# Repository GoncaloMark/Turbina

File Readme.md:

# Turbina '23

Componente Hardware e Software para Turbinas Tesup carregarem baterias de 12V.

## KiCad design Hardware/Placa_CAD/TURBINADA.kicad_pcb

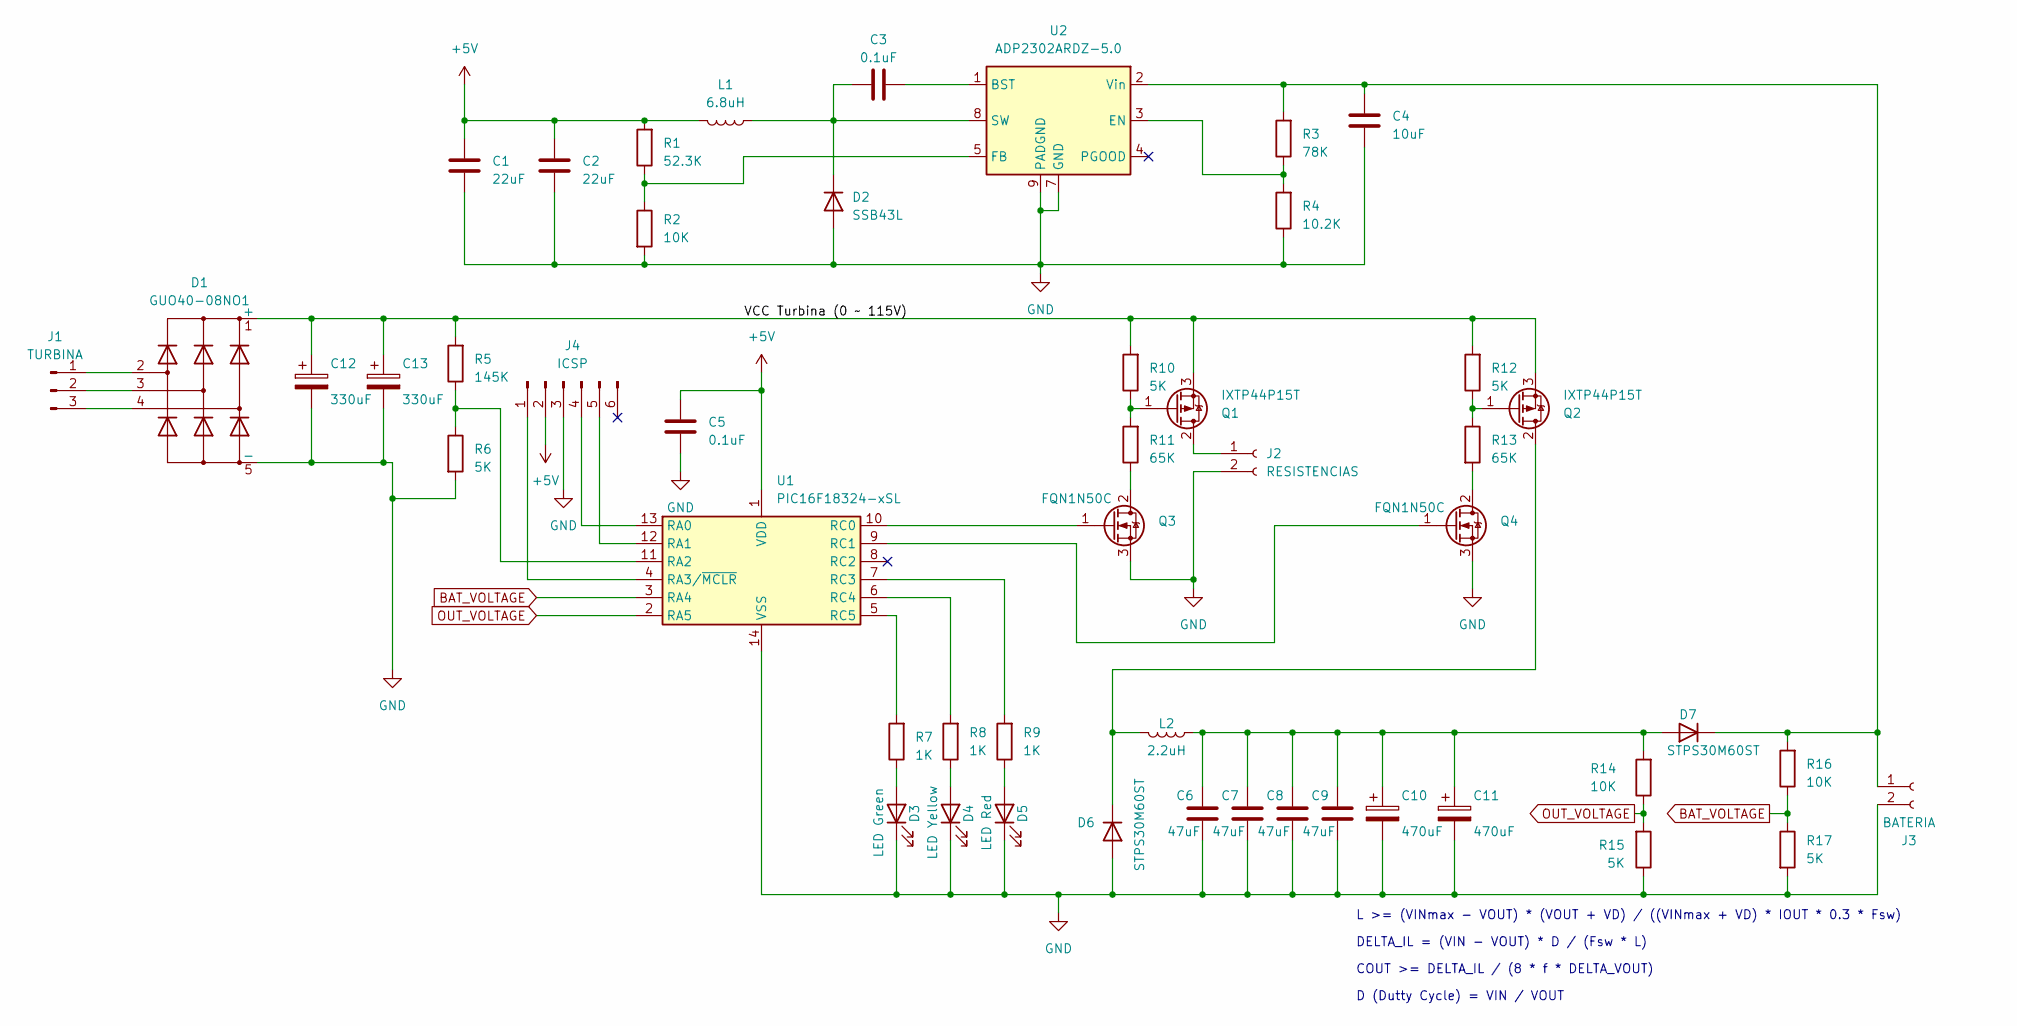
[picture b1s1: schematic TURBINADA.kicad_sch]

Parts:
C1, C2: 22uF; C_Disc_D7.5mm_W5.0mm_P5.00mm; Part FG20X7R1C226MRT00
C3, C5: 0.1uF; C_Disc_D6.0mm_W4.4mm_P5.00mm; Part K104K15X7RF53H5
C4: 10uF; C_Disc_D6.0mm_W4.4mm_P5.00mm; Part FG24X7R1A106KRT06
C6, C7, C8, C9: 47uF; C_Radial_D6.3mm_H5.0mm_P2.50mm; Part FG16X5R1E476MRT06
C10, C11: 470uF; CP_Radial_D13.0mm_P5.00mm; Part ESK477M063AL4AA
C12, C13: 330uF; CP_Radial_D18.0mm_P7.50mm; Part UVY2D331MHD
D1: GUO40-08NO1; Diode_Bridge_IXYS_GUFP; Part GUO40-08NO1
D2: SSB43L; D_SMB_Handsoldering; Part SSB43L
D3: LED Green; LED_D4.0mm; Part C4SMA-GGY-CU2W37A1
D4: LED Yellow; LED_D4.0mm; Part SSL-LX3054OD
D5: LED Red; LED_D4.0mm; Part C4SMA-RGY-CS4V1BB1
D6, D7: STPS30M60ST; TO-220-3_Vertical; Part STPS30M60ST
J1: TURBINA; PhoenixContact_GMSTBA_2,5_3-G_1x03_P7.50mm_Horizontal; Part 1988118
J2: RESISTENCIAS; PhoenixContact_MSTBA_2,5_2-G_1x02_P5.00mm_Horizontal; Part 1987724
J3: BATERIA; TerminalBlock_RND_205-00241_1x02_P10.16mm_Horizontal; Part 1017526
J4: ICSP; PinSocket_1x06_P2.54mm_Vertical
L1: 6.8uH; L_Bourns_SRP1038C_10.0x10.0mm; Part CLF10040T-6R8N-D
L2: 2.2uH; IHXL1500VZEB2R2M51; Part IHXL1500VZEB2R2M51
Q1, Q2: IXTP44P15T; TO-220-3_Vertical; Part IXTP44P15T
Q3, Q4: FQN1N50C; TO-92; Part FQN1N50C
R1: 52.3K; R_Axial_DIN0207_L6.3mm_D2.5mm_P7.62mm_Horizontal; Part MFR-25FBF52-52K3
R2, R14, R16: 10K; R_Axial_DIN0207_L6.3mm_D2.5mm_P7.62mm_Horizontal; Part CMF5510K000FKEK
R3: 78K; R_Axial_DIN0207_L6.3mm_D2.5mm_P7.62mm_Horizontal; Part CMF5578K700FHEB
R4: 10.2K; R_Axial_DIN0207_L6.3mm_D2.5mm_P7.62mm_Horizontal; Part CMF5510K200FHEB
R5: 145K; R_Axial_DIN0207_L6.3mm_D2.5mm_P7.62mm_Horizontal; Part CMF55145K00BER6
R6, R10, R12, R15, R17: 5K; R_Axial_DIN0207_L6.3mm_D2.5mm_P7.62mm_Horizontal; Part CMF555K0000BEEK
R7, R8, R9: 1K; R_Axial_DIN0207_L6.3mm_D2.5mm_P7.62mm_Horizontal; Part MF1/4LCT52R102J
R11, R13: 65K; R_Axial_DIN0207_L6.3mm_D2.5mm_P7.62mm_Horizontal; Part CMF5565K700BHEK
U1: PIC16F18324-xSL; DIP-14_W10.16mm; Part PIC16F18324
U2: ADP2302ARDZ-5.0; SOIC-8-1EP_3.9x4.9mm_P1.27mm_EP2.29x3mm; Part ADP2302ARDZ-5.0

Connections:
+5V: C1.2, C2.2, C5.2, J4.2, L1.2, R1.2, U1.1 (VDD)
/VCC Turbina (0 ~ 115V): C12.1, C13.1, D1.1 (+), Q1.3 (S), Q2.3 (S), R5.2, R10.2, R12.2
BAT_VOLTAGE: R16.1, R17.1, U1.3 (RA4)
GND: C1.1, C2.1, C4.1, C5.1, C6.2, C7.2, C8.2, C9.2, C10.2, C11.2, C12.2, C13.2, D1.5 (-), D2.2 (A), D3.1 (K), D4.1 (K), D5.1 (K), D6.1 (A), D6.3 (A), J2.2, J3.2, J4.3, Q3.3 (S), Q4.3 (S), R2.2, R4.1, R6.2, R15.1, R17.2, U1.14 (VSS), U2.7 (GND), U2.9 (PADGND)
unnamed: C6.1, C7.1, C8.1, C9.1, C10.1, C11.1, D7.1 (A), D7.3 (A), L2.1, R14.2
unnamed: C3.1, D2.1 (K), L1.1, U2.8 (SW)
unnamed: D3.2 (A), R7.1
unnamed: D4.2 (A), R8.1
unnamed: D5.2 (A), R9.1
unnamed: D6.2 (K), L2.2, Q2.2 (D)
unnamed: C4.2, D7.2 (K), J3.1, R3.2, R16.2, U2.2 (Vin)
unnamed: D1.2, J1.1
unnamed: D1.3, J1.2
unnamed: D1.4, J1.3
unnamed: J2.1, Q1.2 (D)
unnamed: J4.1, U1.4 (RA3/~MCLR)
unnamed: J4.4, U1.13 (RA0)
unnamed: J4.5, U1.12 (RA1)
unnamed: Q1.1 (G), R10.1, R11.2
unnamed: Q2.1 (G), R12.1, R13.1
unnamed: Q3.2 (D), R11.1
unnamed: Q3.1 (G), U1.10 (RC0)
unnamed: Q4.2 (D), R13.2
unnamed: Q4.1 (G), U1.9 (RC1)
unnamed: R5.1, R6.1, U1.11 (RA2)
unnamed: R9.2, U1.7 (RC3)
unnamed: R8.2, U1.6 (RC4)
unnamed: R7.2, U1.5 (RC5)
unnamed: C3.2, U2.1 (BST)
unnamed: R3.1, R4.2, U2.3 (EN)
unnamed: R1.1, R2.1, U2.5 (FB)
OUT_VOLTAGE: R14.1, R15.2, U1.2 (RA5)

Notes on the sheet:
COUT >= DELTA_IL / (8 * f * DELTA_VOUT)
L >= (VINmax - VOUT) * (VOUT + VD) / ((VINmax + VD) * IOUT * 0.3 * Fsw)
DELTA_IL = (VIN - VOUT) * D / (Fsw * L)
D (Dutty Cycle) = VIN / VOUT

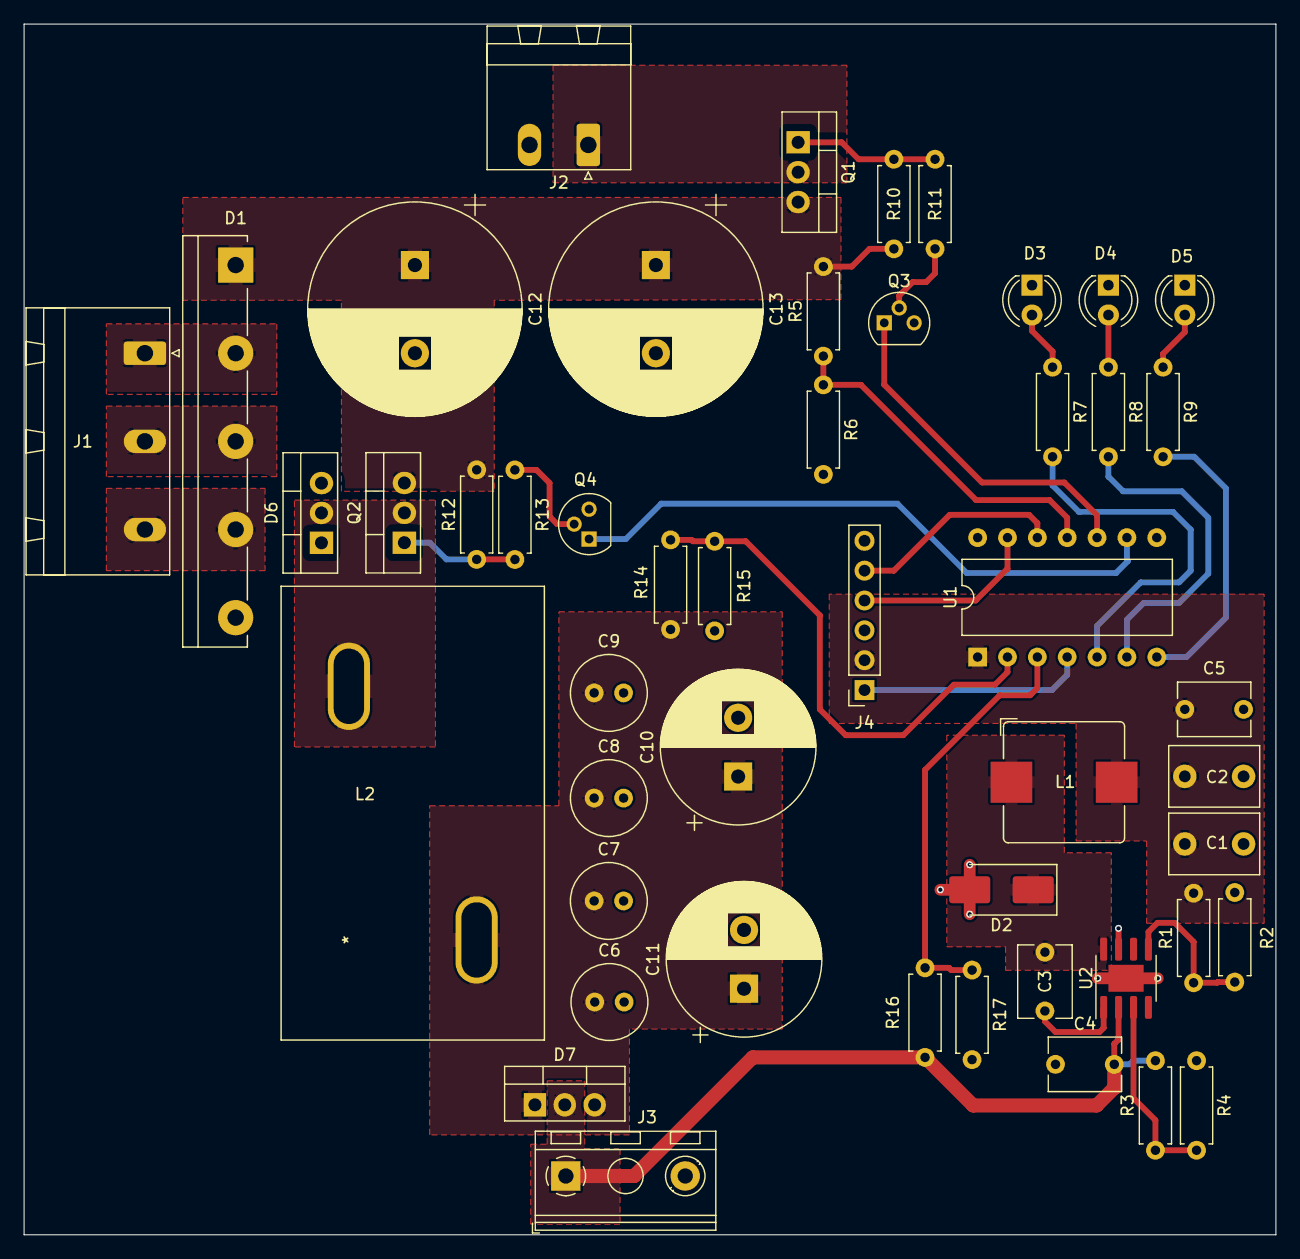
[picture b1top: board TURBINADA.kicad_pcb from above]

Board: 6 copper layers, 106.5 x 103.0 mm, 49 parts (0 on the bottom side), 32 nets.

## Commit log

2023-02-09 First commit, KiCAD (Hardware)
2023-02-09 PCB Design (missing board outline)
2023-03-03 Selected transistor components in schematic
2023-03-15 Selected a few more components and footprints
2023-03-17 All components selected except for the output coil and capacitor
2023-03-17 Delete Hardware/Placa_CAD/TURBINADA-backups directory
    deleting backups directory
2023-03-17 Adding .gitignore
2023-03-28 Selected all components. Started PCB drawing
2023-03-29 Finished board layout
2023-03-29 Fixed a BAT connector track in the layout
2023-03-29 Changed coil footprint
2023-03-29 Corrected some part numbers
2023-04-24 Started I/O firmware implementation drivers
2023-04-24 Added register manipulation to include

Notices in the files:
parts and their libraries:
Copyright 2021 Accelerated Designs. All rights reserved.
